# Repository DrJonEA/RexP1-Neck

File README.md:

# RexP1-Neck

Drive wheel for my RexP1 Astro Droid Project based on a RP2040Zero board. This Repo repreents the drive wheel subsystem for RexP1.

Checkout the [videos guides](https://www.youtube.com/playlist?list=PLspDyukWAtRUPNdlktaOdk7os9TfTEFh1) to the project over on my [YouTube Channel DrJonEA](https://youtube.com/@drjonea).
 
## RexP1 Intro
RexP1 is a reimagined Star War's inspired Astro Droid based on the R series Droids. It is based on Raspberry PI 5, RP2040 and RP2350 boards. It's control system is a distributed net based on ROS2 and MicroROS frameworks.

All my work on RexP1 is available to  my sponsors. That includes not just this submodule but all the submodules, the build instructions, PCB designs, STL files, CAD designs and most important acess to me to ask questions. Take a look at the sponsorship button on the github repo.

## The Repo
This repo includes the PCB design for the dome rotation and tilt  with assoicated documentation. It also includes the firmware for a RP2040Zero which acts as a ROS2 Node to control the Dome.

## Libraries
Note libraries have not been included as submodules in this repo. That is because I wanted just a single copy of the libraries in the master repo for RexP1. So take note of the [lib documentation](docs/Libraries.md).

## Build process
The firmware should build like most *complex* Pico SDK firmware projects. Normal procedure:
```
mkdir build
cd build
cmake ..
make
```
If you have ninja use that instead of make for Windows. Just make sure you update the CMakelists.txt to point to your libraries and that the environment variable PICO_SDK_PATH is defined to point to the SDK.

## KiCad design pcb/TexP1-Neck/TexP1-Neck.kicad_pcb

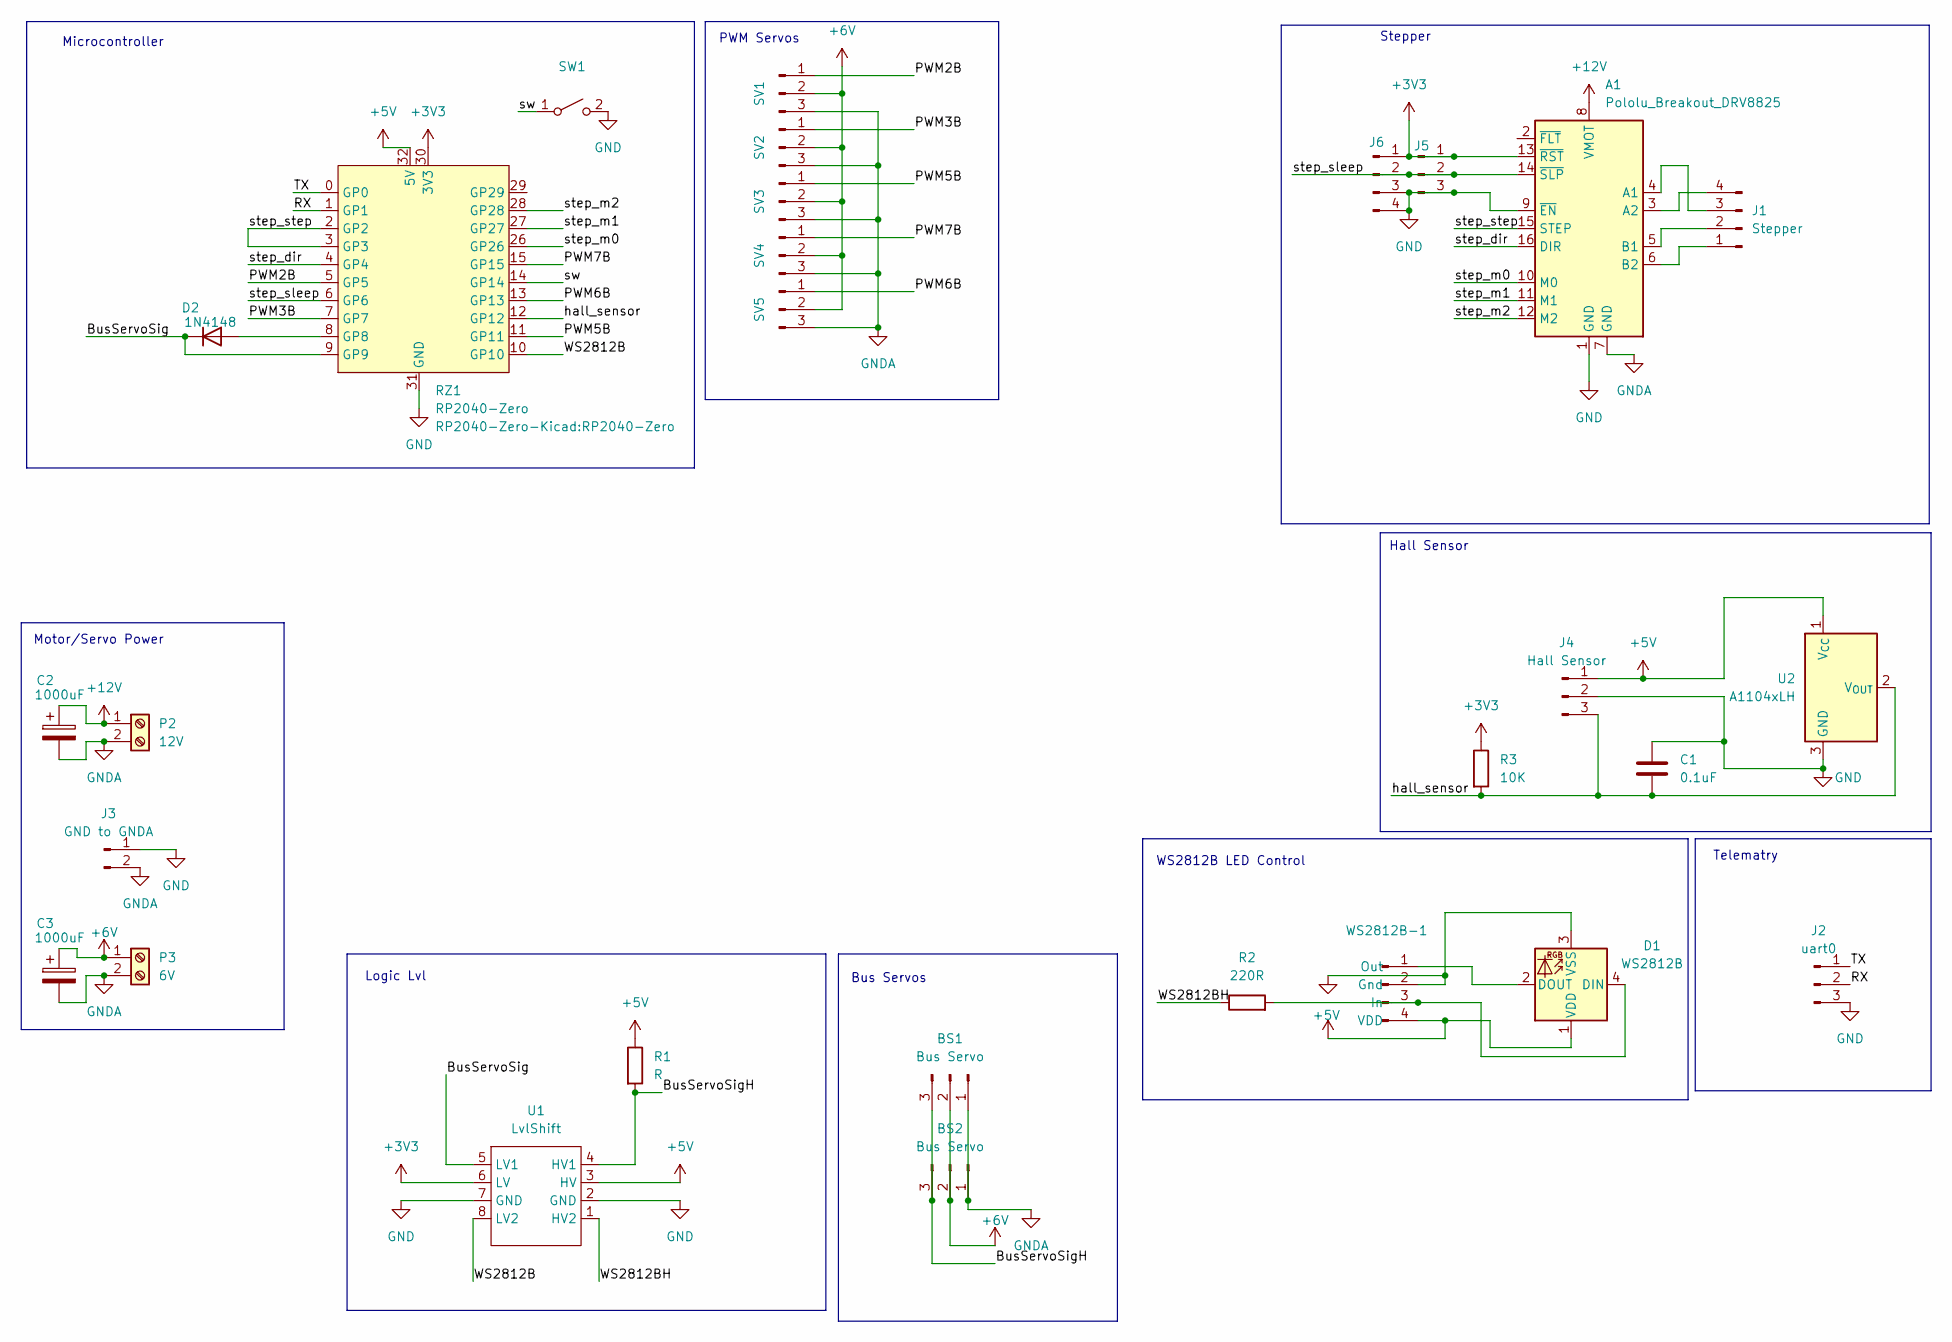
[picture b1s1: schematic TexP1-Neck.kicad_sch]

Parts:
A1: Pololu_Breakout_DRV8825; Pololu_Breakout-16_15.2x20.3mm
BS1, BS2: Bus Servo; JST_XH_B3B-XH-AM_1x03_P2.50mm_Vertical
C1: 0.1uF; C_Disc_D4.7mm_W2.5mm_P5.00mm
C2, C3: 1000uF; CP_Radial_D8.0mm_P5.00mm
D1: WS2812B; LED_WS2812B_PLCC4_5.0x5.0mm_P3.2mm
D2: 1N4148; D_DO-35_SOD27_P7.62mm_Horizontal
J1: Stepper; JST_XH_B4B-XH-AM_1x04_P2.50mm_Vertical
J2: uart0; PinHeader_1x03_P2.54mm_Vertical
J3: GND to GNDA; PinHeader_1x02_P2.54mm_Vertical
J4: Hall Sensor; PinHeader_1x03_P2.54mm_Vertical
J5: Conn_01x03_Pin; PinHeader_1x03_P2.54mm_Vertical
J6: Conn_01x04_Pin; PinHeader_1x04_P2.54mm_Vertical
P2: 12V; SCREWTERMINAL-5MM-2
P3: 6V; SCREWTERMINAL-5MM-2
R1: R; R_Axial_DIN0207_L6.3mm_D2.5mm_P10.16mm_Horizontal
R2: 220R; R_Axial_DIN0207_L6.3mm_D2.5mm_P10.16mm_Horizontal
R3: 10K; R_Axial_DIN0207_L6.3mm_D2.5mm_P10.16mm_Horizontal
RZ1: RP2040-Zero
SV1, SV2, SV3, SV4, SV5: Conn_01x03_Pin; PinHeader_1x03_P2.54mm_Vertical
SW1: SW_SPST; SW_PUSH_6mm
U1: LvlShift; LvlShift2Bi
U2: A1104xLH; SOT-23W
WS2812B-1: Conn_01x04_Pin; PinHeader_1x04_P2.54mm_Vertical

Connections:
+3V3: A1.13 (~RST), J5.1, J6.1, R3.1, RZ1.30 (3V3), U1.6 (LV)
+5V: D1.1 (VDD), J4.1, R1.1, RZ1.32 (5V), U1.3 (HV), U2.1 (V_{CC}), WS2812B-1.4 (VDD)
+6V: BS1.2, BS2.2, C3.1, P3.1, SV1.2, SV2.2, SV3.2, SV4.2, SV5.2
+12V: A1.8 (VMOT), C2.1, P2.1
/BusServoSig: D2.1 (K), RZ1.9 (GP9), U1.5 (LV1)
/BusServoSigH: BS1.3, BS2.3, R1.2, U1.4 (HV1)
/PWM2B: RZ1.5 (GP5), SV1.1
/PWM3B: RZ1.7 (GP7), SV2.1
/PWM5B: RZ1.11 (GP11), SV3.1
/PWM6B: RZ1.13 (GP13), SV5.1
/PWM7B: RZ1.15 (GP15), SV4.1
/RX: J2.2, RZ1.1 (GP1)
/TX: J2.1, RZ1.0 (GP0)
/WS2812B: RZ1.10 (GP10), U1.8 (LV2)
/WS2812BH: R2.1, U1.1 (HV2)
/hall_sensor: C1.2, J4.3, R3.2, RZ1.12 (GP12), U2.2 (V_{OUT})
/step_dir: A1.16 (DIR), RZ1.4 (GP4)
/step_m0: A1.10 (M0), RZ1.26 (GP26)
/step_m1: A1.11 (M1), RZ1.27 (GP27)
/step_m2: A1.12 (M2), RZ1.28 (GP28)
/step_sleep: A1.14 (~SLP), J5.2, J6.2, RZ1.6 (GP6)
/step_step: A1.15 (STEP), RZ1.2 (GP2), RZ1.3 (GP3)
/sw: RZ1.14 (GP14), SW1.1 (A)
GND: A1.1 (GND), A1.9 (~EN), C1.1, D1.3 (VSS), J2.3, J3.1, J4.2, J5.3, J6.3, J6.4, RZ1.31 (GND), SW1.2 (B), U1.2 (GND), U1.7 (GND), U2.3 (GND), WS2812B-1.2 (Gnd)
GNDA: A1.7 (GND), BS1.1, BS2.1, C2.2, C3.2, J3.2, P2.2, P3.2, SV1.3, SV2.3, SV3.3, SV4.3, SV5.3
unnamed: A1.4 (A1), J1.3
unnamed: A1.3 (A2), J1.4
unnamed: A1.5 (B1), J1.2
unnamed: A1.6 (B2), J1.1
unnamed: D2.2 (A), RZ1.8 (GP8)
unnamed: D1.4 (DIN), R2.2, WS2812B-1.3 (In)
unnamed: D1.2 (DOUT), WS2812B-1.1 (Out)

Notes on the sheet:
Telematry
PWM Servos
Bus Servos
Logic Lvl
Hall Sensor
WS2812B LED Control
Stepper
Microcontroller
Motor/Servo Power

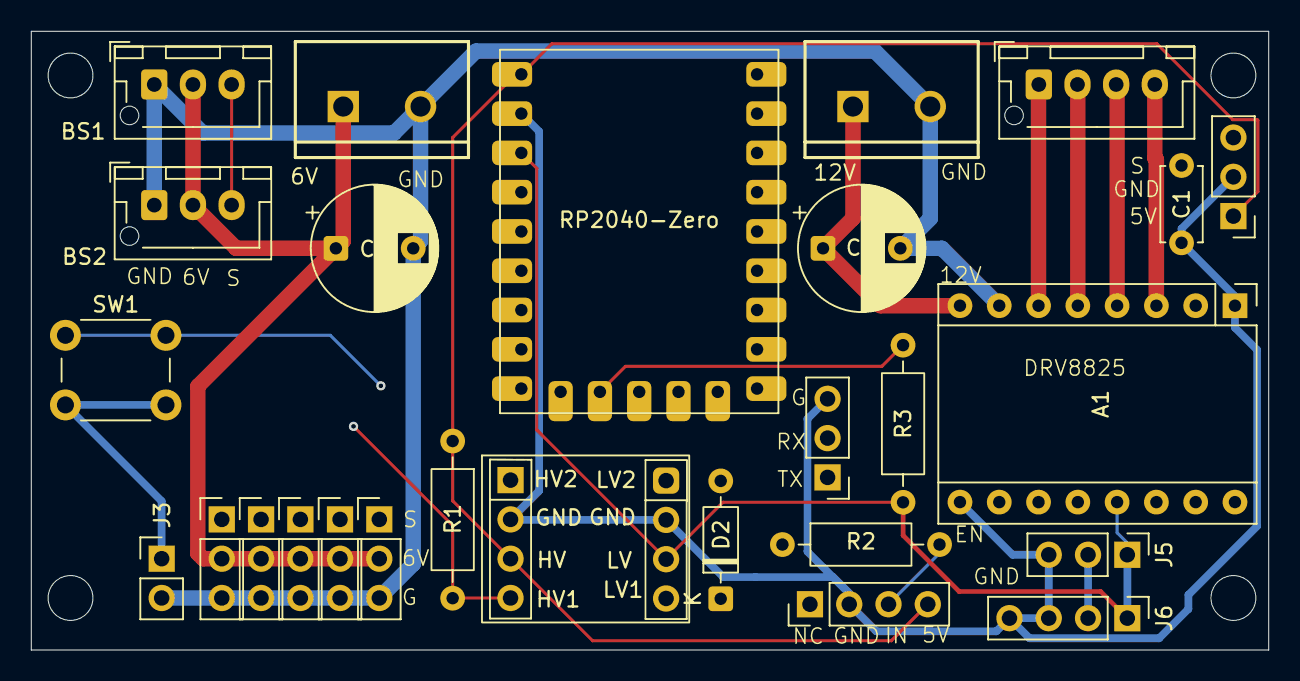
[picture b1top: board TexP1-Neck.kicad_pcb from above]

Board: 4 copper layers, 80.0 x 40.0 mm, 27 parts (0 on the bottom side), 31 nets.

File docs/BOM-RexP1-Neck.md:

# Bill of Materials

This is a BOM for the controller PCB. Headerpins will also be needed for some of the connectors.


|Reference |Footprint	 |	Qty	| Link | Notes
|----------|----------|----|--------|-------|
|A1|Pololu_Breakout_DRV8825| 1|https://amzn.to/3GIwLjC||
|BS1,BS2|JST_XH_B3B-XH-AM_1x03_P2.50mm_Vertical|2| | For HiWonder LX16A|
|C1|0.1uF C_Disc_D4.7mm_W2.5mm_P5.00mm|1|||
|C2,C3|1000uF CP_Radial_D8.0mm_P5.00mm|2|||
|D2|1N4148|1|https://assets.nexperia.com/documents/data-sheet/1N4148_1N4448.pdff|||
|J1|Stepper JST_XH_B4B-XH-AM_1x04_P2.50mm_Vertical|1|||
|J2|uart0 PinHeader_1x03_P2.54mm_Vertical,"1"|||
|J3|GND to GNDA PinHeader_1x02_P2.54mm_Vertical|1||Allows jumper to connect grounds|
|J4|Hall Sensor PinHeader_1x03_P2.54mm_Vertical|1|||
|J5,SV1,SV2,SV3,SV4,SV5| PinHeader_1x03_P2.54mm_Vertical|6||Used for Servos|
|J6| WS2812B-1 Conn_01x04_Pin|2|||
|P2|12V SCREWTERMINAL-5MM-2|1|||
|P3|6V|SCREWTERMINAL-5MM-2|1|||
|R1|RResistor_THT|1|||
|R2|220R|Resistor_THT|1|||
|R3|10K|Resistor_THT|1|||
|RZ1|RP2040-Zero|RP2040-Zero||1||
|SW1|SW_SPST |1|SW_PUSH_6mm||
|U1|LvlShift2Bi||1|| 2 channel level shifter|
|U2|A1104xLH|1|HAll Sensor||

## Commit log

2025-07-14 Added to new home

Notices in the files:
pcb/TexP1-Neck/TexP1-Neck.kicad_pcb:
(C) 2025 Dr Jon EA Ltd
